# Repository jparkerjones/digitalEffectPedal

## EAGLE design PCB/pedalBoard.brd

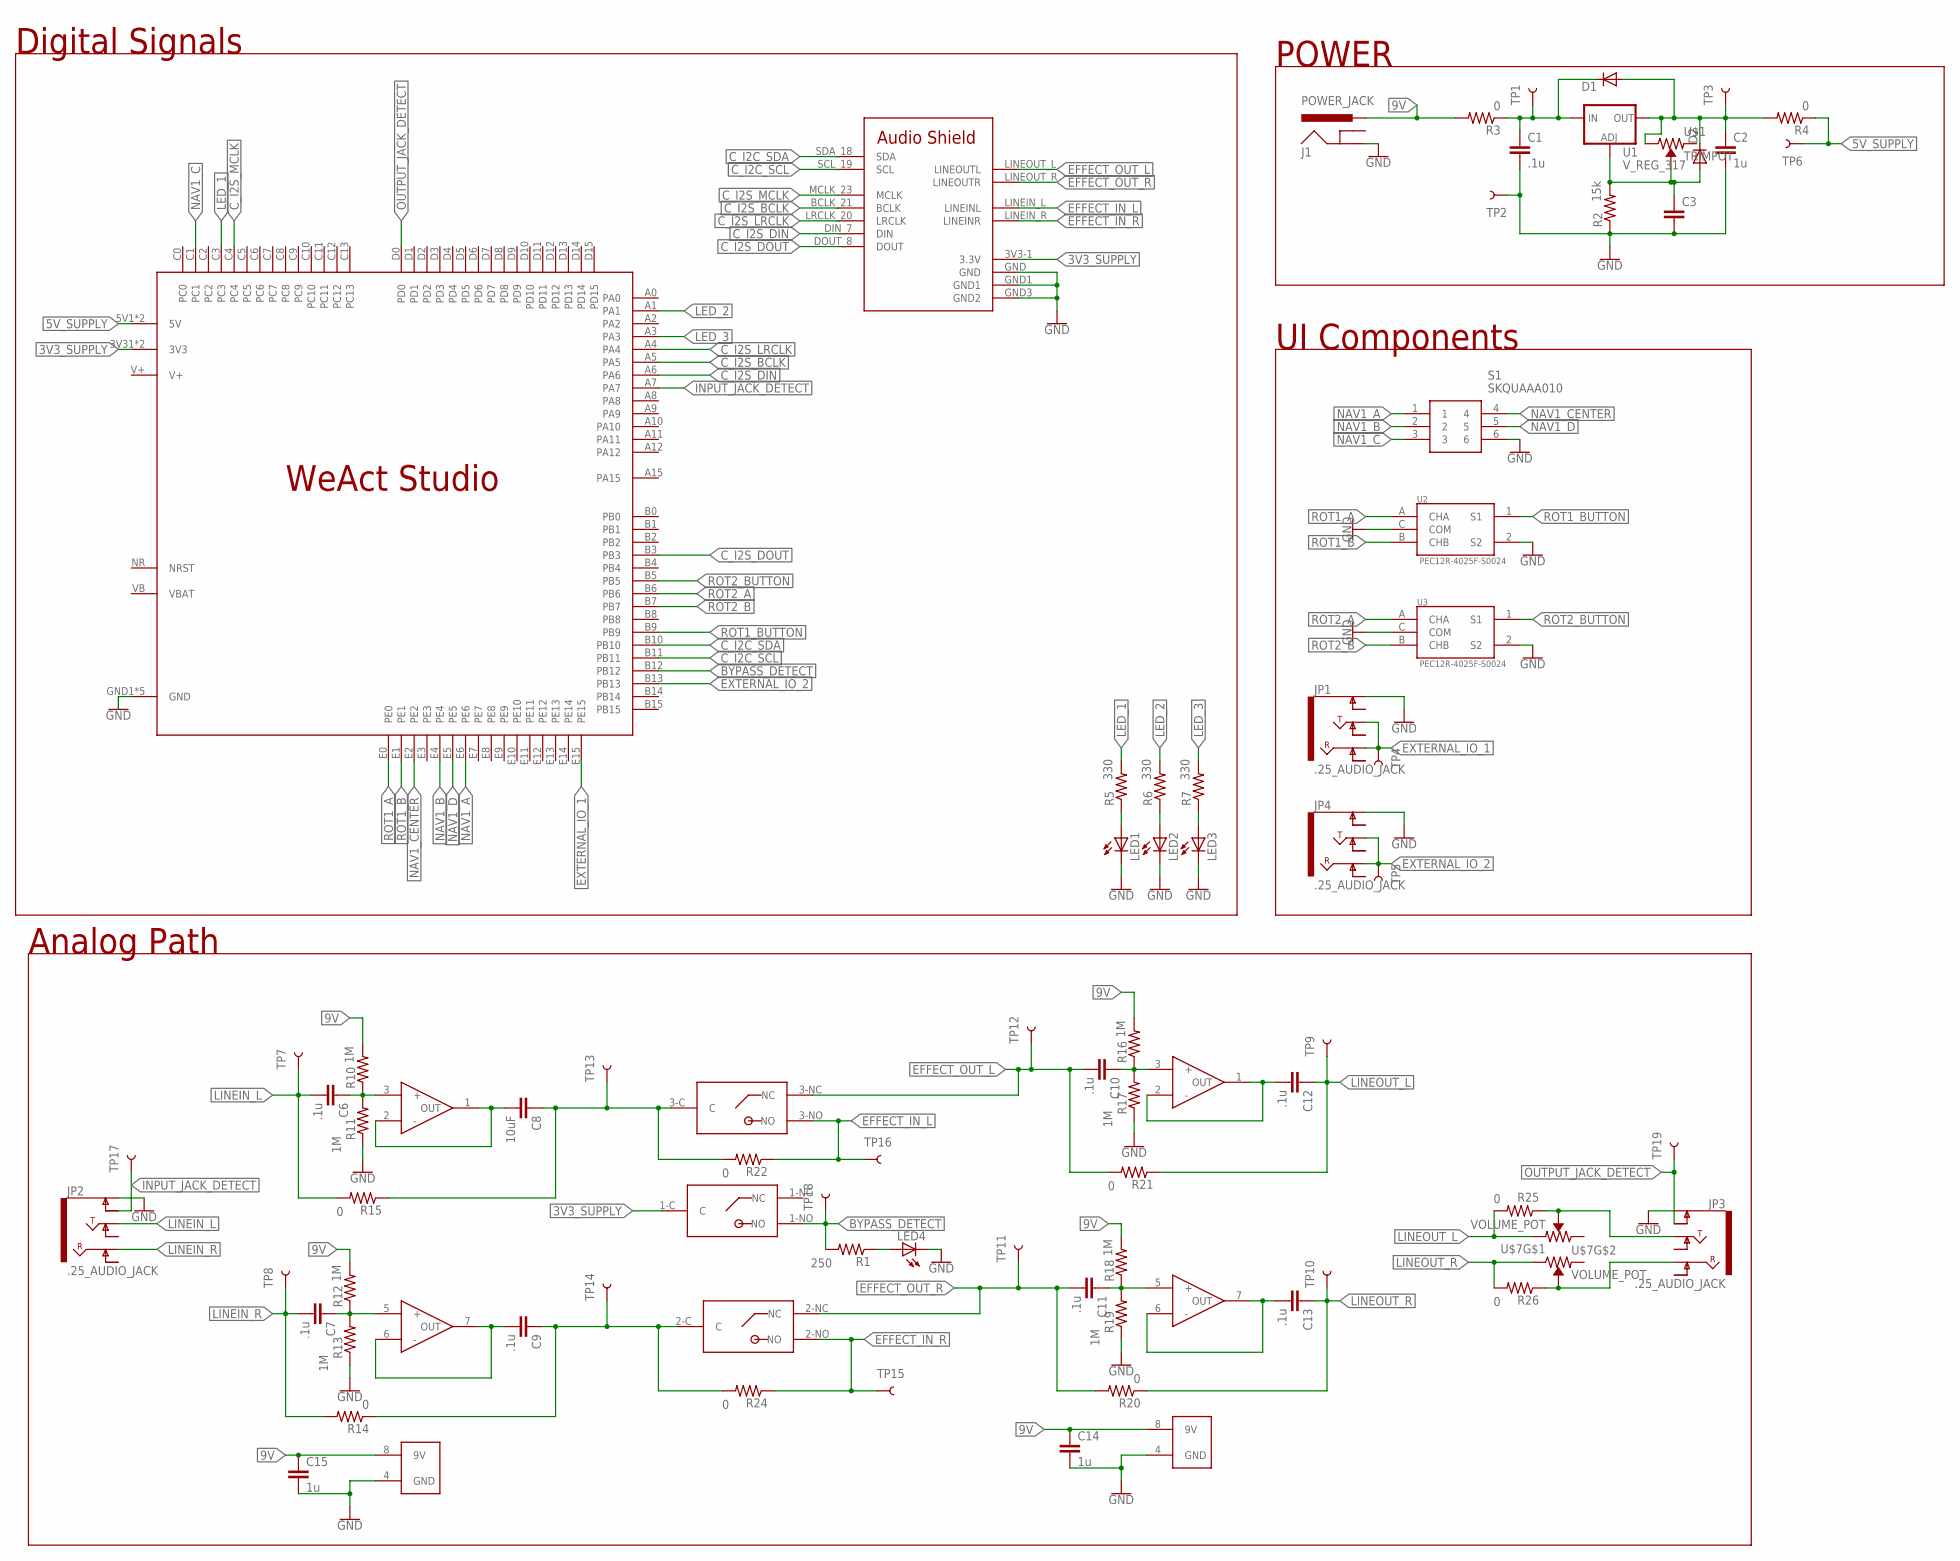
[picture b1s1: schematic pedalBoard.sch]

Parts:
C1, C6, C7, C9, C10, C11, C12, C13: .1u; C5B3
C2, C14, C15: 1u; C5B3
C3: C5/3; C5B3
C8: 10uF; C5B3
D1, D2: 1N4004; DO41-10
J1: POWER_JACK; POWER_JACK_PTH
JP1, JP2, JP3, JP4: .25_AUDIO_JACK; SPARKFUN-CONNECTORS_AUDIO-JACK-.25-INCH-HORIZ-PTH
LED1, LED2, LED3, LED4: LED3MM
R1: 250; ADAFRUIT_0309/12
R2: 15k; ADAFRUIT_0309/12
R3, R4, R14, R15, R20, R21, R22, R24, R25, R26: 0; ADAFRUIT_0309/12
R5, R6, R7: 330; ADAFRUIT_0309/12
R10, R11, R12, R13, R16, R17, R18, R19: 1M; ADAFRUIT_0309/12
S1: SKQUAAA010
TP1, TP2, TP3, TP4, TP5, TP6, TP7, TP8, TP9, TP10, TP11, TP12, TP13, TP14, TP15, TP16, TP17, TP18, TP19: TEST-POINT3X5; PAD.03X.05
U1: V_REG_317; TO220
U2, U3: PEC12R-4025F-S0024; ENC_PEC12R-4025F-S0024
U$1: TRIMPOT
U$2: STOMP_SWITCH
U$3: AUDIO_SHIELD
U$4: WEACT_STUDIO
U$5, U$6: TL072; 8S1
U$7: VOLUME_POT; 2X3

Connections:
3V3_SUPPLY: U$2.1-C (C), U$3.3V3-1 (3.3V), U$4.3V31 (3V3), U$4.3V32 (3V3)
5V_SUPPLY: R4.1, TP6.P$1, U$4.5V1 (5V), U$4.5V2 (5V)
9V: C14.1, C15.1, J1.GND (PWR), R3.2, R10.2, R12.2, R16.2, R18.2, U$5.8 (9V), U$6.8 (9V)
BUFFERED_L: C8.1, R15.1, R22.2, TP13.P$1, U$2.3-C (C)
BUFFERED_R: C9.1, R14.1, R24.2, TP14.P$1, U$2.2-C (C)
BYPASS_DETECT: R1.2, TP18.P$1, U$2.1-NO (NO), U$4.B12
C_I2C_SCL: U$3.SCL_19 (SCL), U$4.B11
C_I2C_SDA: U$3.SDA_18 (SDA), U$4.B10
C_I2S_BCLK: U$3.BCLK_21 (BCLK), U$4.A5
C_I2S_DIN: U$3.DIN_7 (DIN), U$4.A6
C_I2S_DOUT: U$3.DOUT_8 (DOUT), U$4.B3
C_I2S_LRCLK: U$3.LRCLK_20 (LRCLK), U$4.A4
C_I2S_MCLK: U$3.MCLK_23 (MCLK), U$4.C4
EFFECT_IN_L: R22.1, TP16.P$1, U$2.3-NO (NO), U$3.LINEIN_L (LINEINL)
EFFECT_IN_R: R24.1, TP15.P$1, U$2.2-NO (NO), U$3.LINEIN_R (LINEINR)
EFFECT_OUT_L: C10.2, R21.2, TP12.P$1, U$2.3-NC (NC), U$3.LINEOUT_L (LINEOUTL)
EFFECT_OUT_R: C11.2, R20.2, TP11.P$1, U$2.2-NC (NC), U$3.LINEOUT_R (LINEOUTR)
EXTERNAL_IO_1: JP1.RING, JP1.TIP, TP4.P$1, U$4.E15
EXTERNAL_IO_2: JP4.RING, JP4.TIP, TP5.P$1, U$4.B13
GND: C1.2, C2.2, C3.2, C14.2, C15.2, J1.PWR (GND), JP1.SLEEVE (EARTH), JP2.SLEEVE (EARTH), JP3.SLEEVE (EARTH), JP4.SLEEVE (EARTH), LED1.K (C), LED2.K (C), LED3.K (C), LED4.K (C), R2.1, R11.1, R13.1, R17.1, R19.1, S1.6, TP2.P$1, U2.2 (S2), U2.C (COM), U3.2 (S2), U3.C (COM), U$3.GND, U$3.GND1, U$3.GND3 (GND2), U$4.GND1 (GND), U$4.GND2 (GND), U$4.GND3 (GND), U$4.GND4 (GND), U$4.GND5 (GND), U$5.4 (GND), U$6.4 (GND)
INPUT_JACK_DETECT: JP2.SLEEVE-NORM (EARTH-NORM), TP17.P$1, U$4.A7
LED_1: R5.2, U$4.C3
LED_2: R6.2, U$4.A1
LED_3: R7.2, U$4.A3
LINEIN_L: C6.2, JP2.TIP, R15.2, TP7.P$1
LINEIN_R: C7.2, JP2.RING, R14.2, TP8.P$1
LINEOUT_L: C12.1, JP3.TIP, R21.1, R25.1, TP9.P$1, U$7.2 (WIPER)
LINEOUT_R: C13.1, JP3.RING, R20.1, R26.1, TP10.P$1, U$7.5 (WIPER)
unnamed: LED1.A, R5.1
unnamed: C1.1, D1.C, R3.1, TP1.P$1, U1.3 (IN)
unnamed: C3.1, D2.A, R2.2, U1.1 (ADJ), U$1.P$3 (WIPER)
unnamed: LED2.A, R6.1
unnamed: LED3.A, R7.1
unnamed: C2.1, D1.A, D2.C, R4.2, TP3.P$1, U1.2 (OUT), U$1.P$2 (CW)
unnamed: C7.1, R12.1, R13.2, U$5.5 (+)
unnamed: C6.1, R10.1, R11.2, U$5.3 (+)
unnamed: C8.2, U$5.1 (OUT), U$5.2 (-)
unnamed: C10.1, R16.1, R17.2, U$6.3 (+)
unnamed: C9.2, U$5.6 (-), U$5.7 (OUT)
unnamed: C12.2, U$6.1 (OUT), U$6.2 (-)
unnamed: C11.1, R18.1, R19.2, U$6.5 (+)
unnamed: C13.2, U$6.6 (-), U$6.7 (OUT)
unnamed: LED4.A, R1.1
unnamed: R25.2, U$7.1 (CCW)
unnamed: R26.2, U$7.6 (CW)
NAV1_A: S1.1, U$4.E6
NAV1_B: S1.2, U$4.E4
NAV1_C: S1.3, U$4.C1
NAV1_CENTER: S1.4, U$4.E2
NAV1_D: S1.5, U$4.E5
OUTPUT_JACK_DETECT: JP3.SLEEVE-NORM (EARTH-NORM), TP19.P$1, U$4.D0
ROT1_A: U2.A (CHA), U$4.E0
ROT1_B: U2.B (CHB), U$4.E1
ROT1_BUTTON: U2.1 (S1), U$4.B9
ROT2_A: U3.A (CHA), U$4.B6
ROT2_B: U3.B (CHB), U$4.B7
ROT2_BUTTON: U3.1 (S1), U$4.B5

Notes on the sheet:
POWER
Digital Signals
Analog Path
UI Components

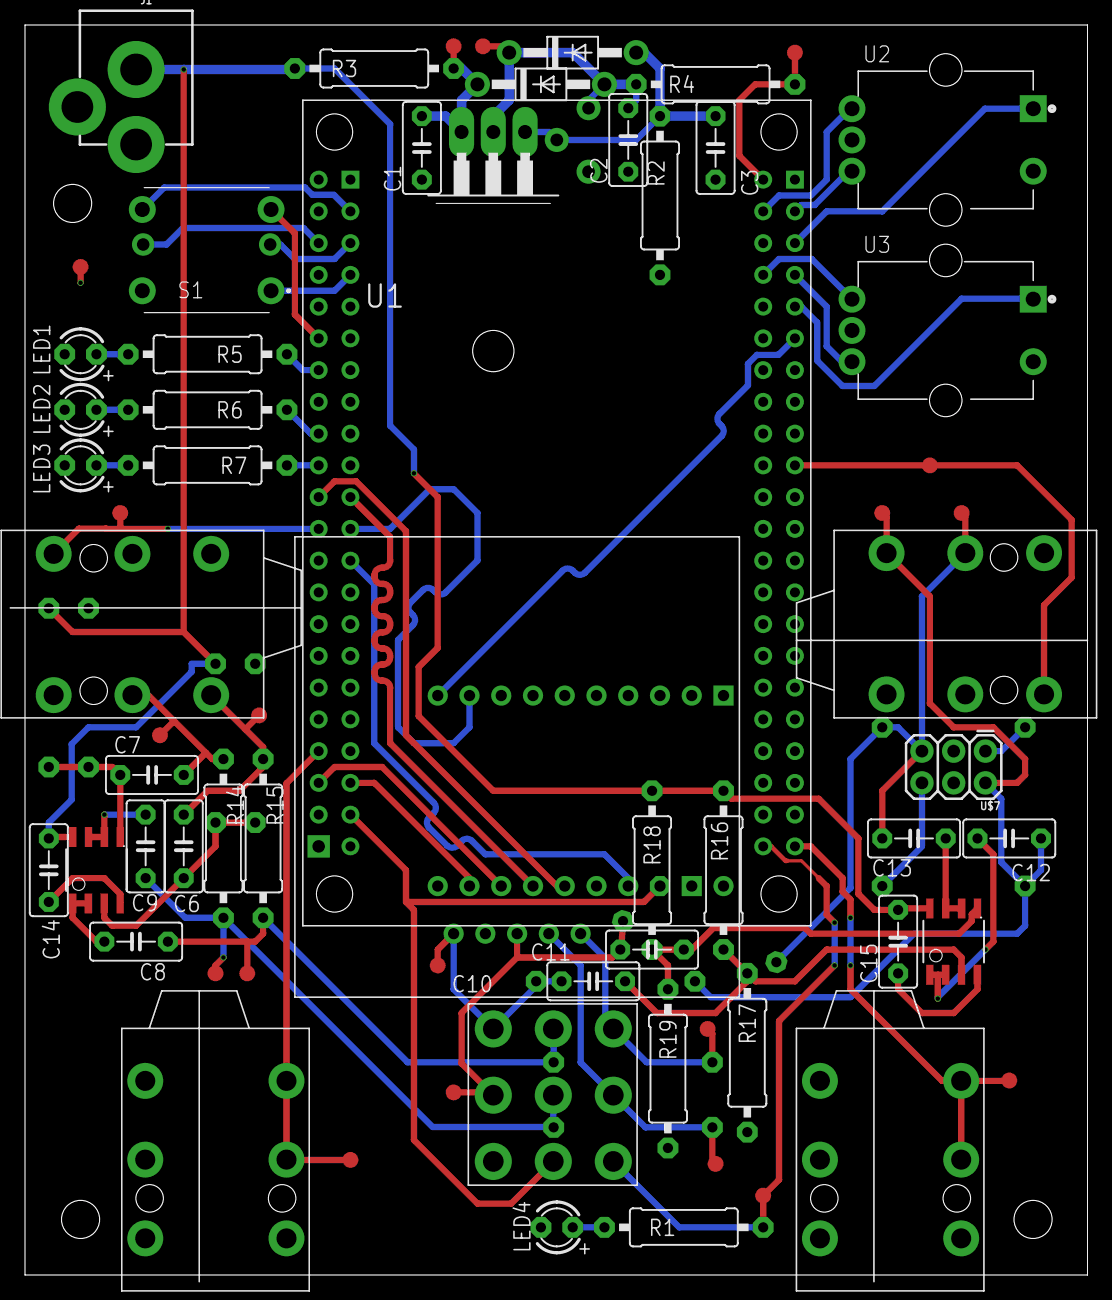
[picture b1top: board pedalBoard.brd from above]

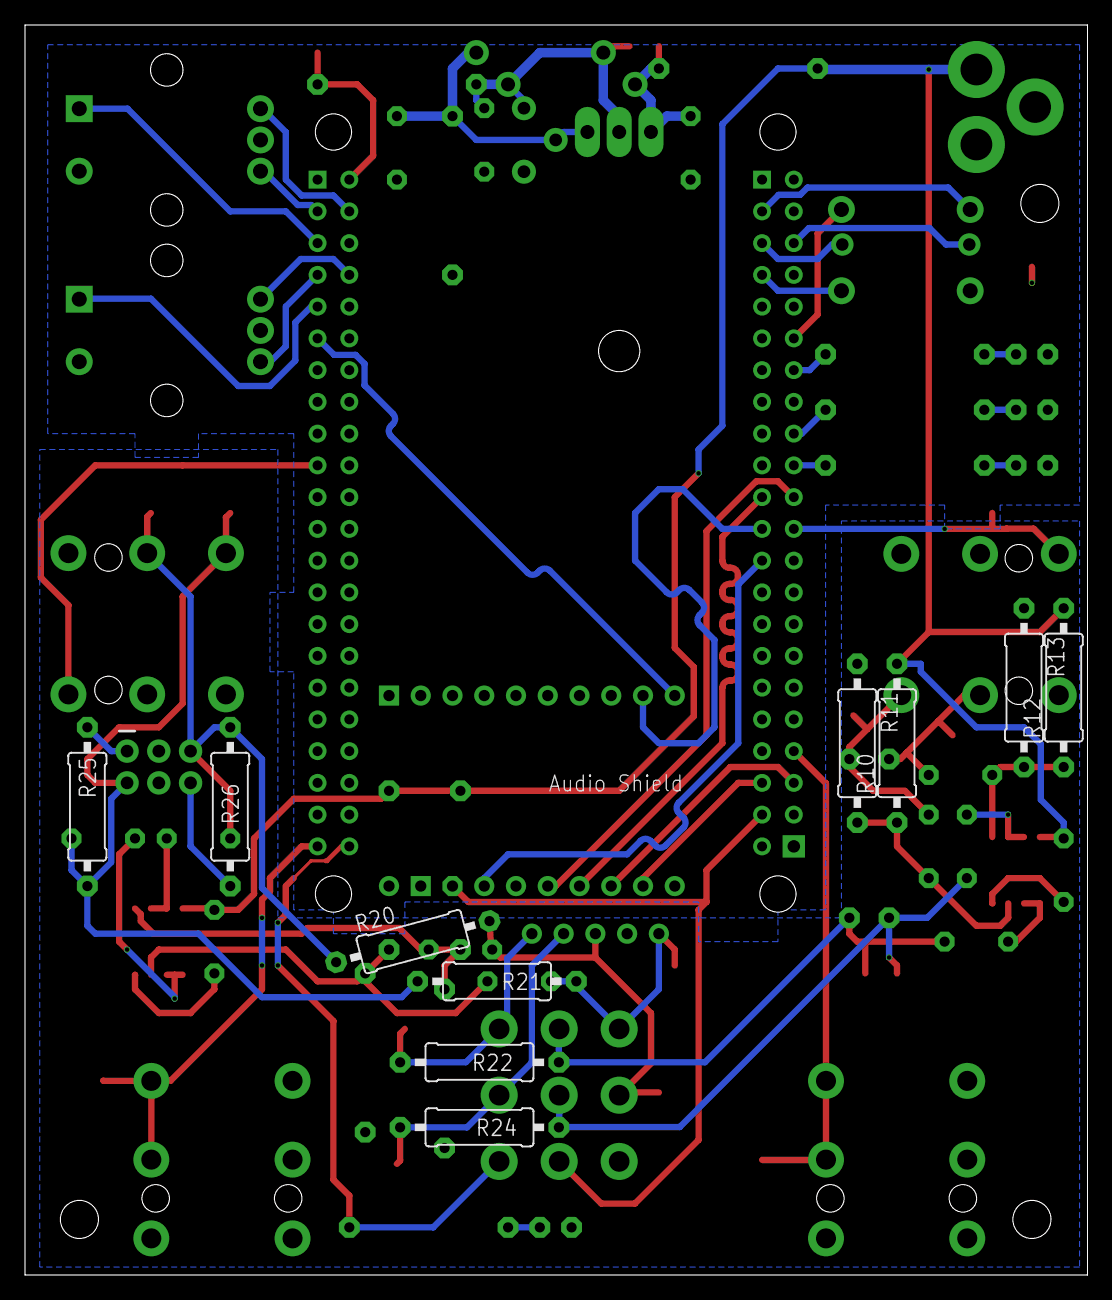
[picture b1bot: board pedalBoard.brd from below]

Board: 2 copper layers, 85.0 x 100.0 mm, 77 parts (11 on the bottom side), 57 nets.

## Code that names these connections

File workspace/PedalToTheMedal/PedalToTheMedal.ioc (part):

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Mcu.Name=STM32H750VBTx
Mcu.Package=LQFP100
Mcu.UserName=STM32H750VBTx
PA1.GPIOParameters=GPIO_Label
PA1.GPIO_Label=LED2
PA1.Signal=GPIO_Output
PA13\ (JTMS/SWDIO).Mode=Serial_Wire
PA13\ (JTMS/SWDIO).Signal=DEBUG_JTMS-SWDIO
PA14\ (JTCK/SWCLK).Mode=Serial_Wire
PA14\ (JTCK/SWCLK).Signal=DEBUG_JTCK-SWCLK
PA3.GPIOParameters=GPIO_Label
PA3.GPIO_Label=LED3
PA3.Signal=GPIO_Output
PA4.Mode=Full_Duplex_Master
PA4.Signal=I2S1_WS
PA5.Mode=Full_Duplex_Master
PA5.Signal=I2S1_CK
PA6.Mode=Full_Duplex_Master
PA6.Signal=I2S1_SDI
PA7.GPIOParameters=GPIO_Label
PA7.GPIO_Label=INPUT_JACK_DETECT
PA7.Signal=GPIO_Input
PB10.Mode=I2C
PB10.Signal=I2C2_SCL
PB11.Mode=I2C
PB11.Signal=I2C2_SDA
PB12.GPIOParameters=GPIO_PuPd,GPIO_Label
PB12.GPIO_Label=BYPASS_DETECT
PB12.GPIO_PuPd=GPIO_PULLDOWN
PB12.Signal=GPIO_Input
PB13.GPIOParameters=GPIO_PuPd,GPIO_Label
PB13.GPIO_Label=EXTERNAL_IO_2
PB13.GPIO_PuPd=GPIO_PULLUP
PB13.Signal=GPIO_Input
PB5.GPIOParameters=GPIO_Label
PB5.GPIO_Label=ROT2_BUTTON
PB5.Signal=GPIO_Input
PB6.GPIOParameters=GPIO_PuPd,GPIO_Label,GPIO_ModeDefaultEXTI
PB6.GPIO_Label=ROT2_A
PB6.GPIO_ModeDefaultEXTI=GPIO_MODE_IT_FALLING
PB6.GPIO_PuPd=GPIO_PULLUP
PB6.Signal=GPXTI6
PB7.GPIOParameters=GPIO_PuPd,GPIO_Label,GPIO_ModeDefaultEXTI
PB7.GPIO_Label=ROT2_B
PB7.GPIO_ModeDefaultEXTI=GPIO_MODE_IT_FALLING
PB7.GPIO_PuPd=GPIO_PULLUP
PB7.Signal=GPXTI7
PB9.GPIOParameters=GPIO_Label
PB9.GPIO_Label=ROT1_BUTTON
PB9.Signal=GPIO_Input
PC1.GPIOParameters=GPIO_PuPd,GPIO_Label
PC1.GPIO_Label=NAV1_C
PC1.GPIO_PuPd=GPIO_PULLUP
PC1.Signal=GPIO_Input
PC13.GPIOParameters=GPIO_PuPd,GPIO_Label
PC13.GPIO_Label=KEY
PC13.GPIO_PuPd=GPIO_PULLDOWN
PC13.Signal=GPIO_Input
PC14-OSC32_IN\ (OSC32_IN).Mode=LSE-External-Oscillator
PC14-OSC32_IN\ (OSC32_IN).Signal=RCC_OSC32_IN
PC15-OSC32_OUT\ (OSC32_OUT).Mode=LSE-External-Oscillator
PC15-OSC32_OUT\ (OSC32_OUT).Signal=RCC_OSC32_OUT
PC3_C.GPIOParameters=GPIO_Label
PC3_C.GPIO_Label=LED1
PC3_C.Signal=GPIO_Output
PC4.Mode=Master_Clock_Activated
PC4.Signal=I2S1_MCK
PD0.GPIOParameters=GPIO_PuPd,GPIO_Label
PD0.GPIO_Label=Output Jack Detect
PD0.GPIO_PuPd=GPIO_PULLUP
PD0.Signal=GPIO_Input
PD7.Mode=Full_Duplex_Master
PD7.Signal=I2S1_SDO
PE0.GPIOParameters=GPIO_PuPd,GPIO_Label,GPIO_ModeDefaultEXTI
PE0.GPIO_Label=ROT1_A
PE0.GPIO_ModeDefaultEXTI=GPIO_MODE_IT_FALLING
PE0.GPIO_PuPd=GPIO_PULLUP
PE0.Signal=GPXTI0
PE1.GPIOParameters=GPIO_PuPd,GPIO_Label,GPIO_ModeDefaultEXTI
PE1.GPIO_Label=ROT1_B
PE1.GPIO_ModeDefaultEXTI=GPIO_MODE_IT_FALLING
PE1.GPIO_PuPd=GPIO_PULLUP
PE1.Signal=GPXTI1
PE10.Mode=PWM Generation2 CH2N
PE10.Signal=TIM1_CH2N
PE11.GPIOParameters=GPIO_Speed,PinState,GPIO_Label
PE11.GPIO_Label=LCD_CS
PE11.GPIO_Speed=GPIO_SPEED_FREQ_VERY_HIGH
PE11.PinState=GPIO_PIN_SET
PE11.Signal=GPIO_Output
PE12.GPIOParameters=GPIO_Speed
PE12.GPIO_Speed=GPIO_SPEED_FREQ_HIGH
PE12.Mode=Simplex_Bidirectional_Master
PE12.Signal=SPI4_SCK
PE13.GPIOParameters=GPIO_Speed,PinState,GPIO_Label
PE13.GPIO_Label=LCD_WR_RS
PE13.GPIO_Speed=GPIO_SPEED_FREQ_VERY_HIGH
PE13.PinState=GPIO_PIN_SET
PE13.Signal=GPIO_Output
PE14.GPIOParameters=GPIO_Speed
PE14.GPIO_Speed=GPIO_SPEED_FREQ_HIGH
PE14.Mode=Simplex_Bidirectional_Master
PE14.Signal=SPI4_MOSI
PE15.GPIOParameters=GPIO_PuPd,GPIO_Label
PE15.GPIO_Label=EXTERNAL_IO_1
PE15.GPIO_PuPd=GPIO_PULLUP
PE15.Signal=GPIO_Input
PE2.GPIOParameters=GPIO_Label
PE2.GPIO_Label=NAV1_CENTER
PE2.Signal=GPIO_Input
PE3.GPIOParameters=PinState,GPIO_Label
PE3.GPIO_Label=E3
PE3.PinState=GPIO_PIN_RESET
PE3.Signal=GPIO_Output
PE4.GPIOParameters=GPIO_PuPd,GPIO_Label
PE4.GPIO_Label=NAV1_B
PE4.GPIO_PuPd=GPIO_PULLUP
PE4.Signal=GPIO_Input
PE5.GPIOParameters=GPIO_PuPd,GPIO_Label
PE5.GPIO_Label=NAV1_D
PE5.GPIO_PuPd=GPIO_PULLUP
PE5.Signal=GPIO_Input
PE6.GPIOParameters=GPIO_PuPd,GPIO_Label
PE6.GPIO_Label=NAV1_A
PE6.GPIO_PuPd=GPIO_PULLUP
PE6.Signal=GPIO_Input
PH0-OSC_IN\ (PH0).Mode=HSE-External-Oscillator
PH0-OSC_IN\ (PH0).Signal=RCC_OSC_IN
PH1-OSC_OUT\ (PH1).Mode=HSE-External-Oscillator
PH1-OSC_OUT\ (PH1).Signal=RCC_OSC_OUT
RCC.HSE_VALUE=25000000
RCC.SYSCLKFreq_VALUE=240000000
RCC.SYSCLKSource=RCC_SYSCLKSOURCE_PLLCLK
board=custom

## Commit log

2022-05-08 Added all files from Senior Design enterprise repo

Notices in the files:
parts and their libraries:
SparkFun-Connectors: Licensing: Creative Commons ShareAlike 4.0 International - https://creativecommons.org/licenses/by-sa/4.0
